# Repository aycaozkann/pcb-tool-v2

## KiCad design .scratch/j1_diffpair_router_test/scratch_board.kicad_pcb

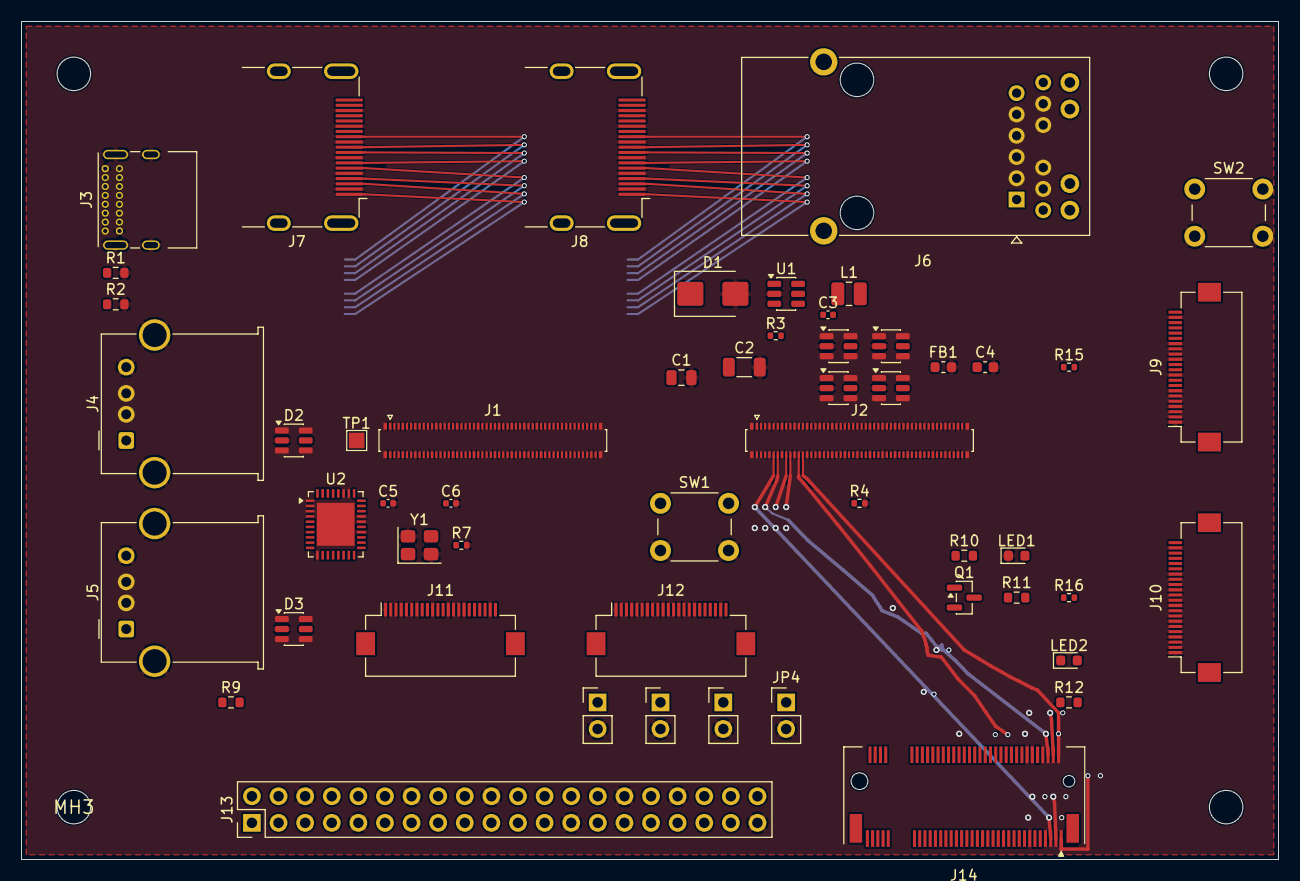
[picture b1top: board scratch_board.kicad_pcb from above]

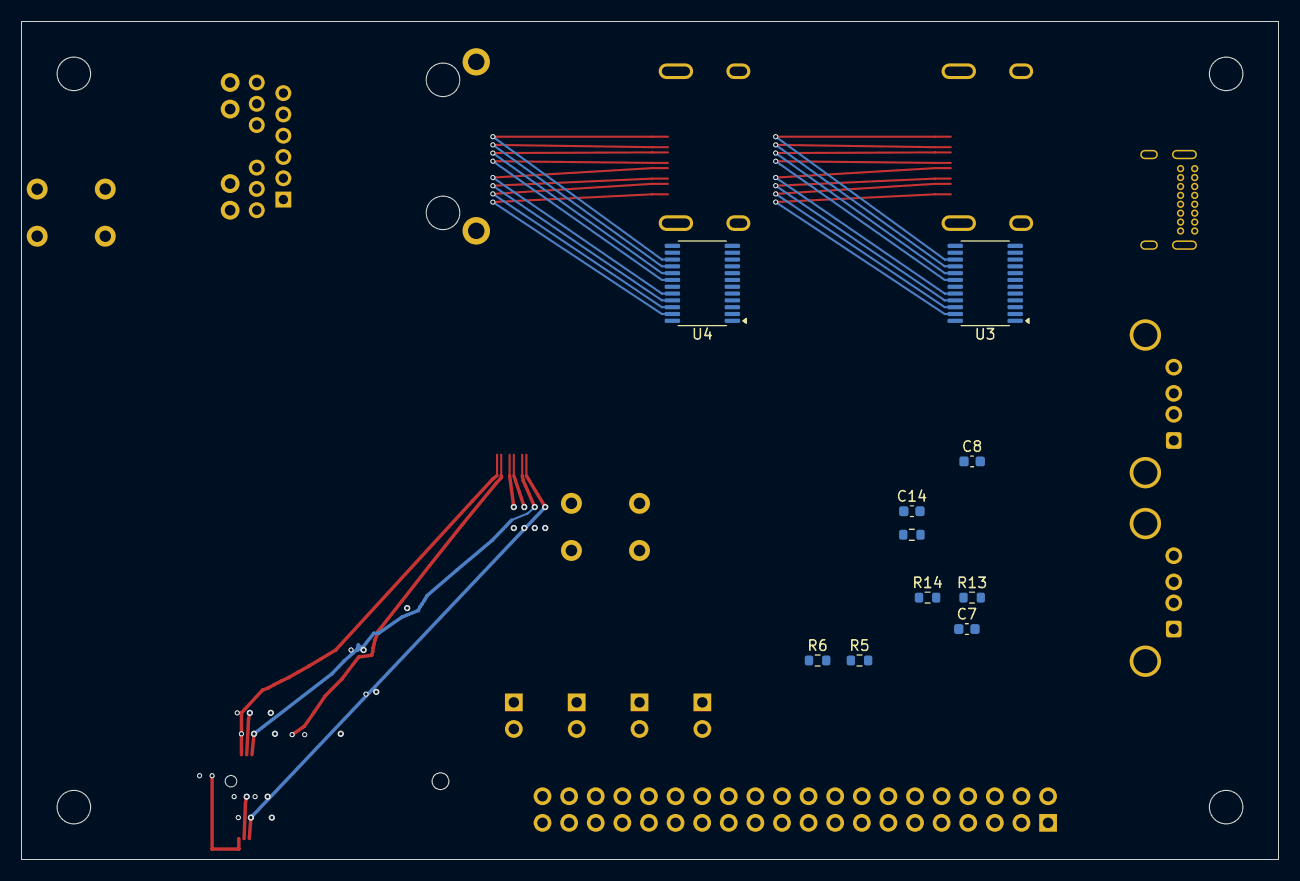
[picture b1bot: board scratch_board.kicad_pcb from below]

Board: 4 copper layers, 120.0 x 80.0 mm, 67 parts (10 on the bottom side), 155 nets.

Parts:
C1: 10uF; C_0805_2012Metric
C2: 22uF; C_1206_3216Metric
C3: 10pF; C_0402_1005Metric
C4: 100nF; C_0603_1608Metric
C5, C6: 15pF; C_0402_1005Metric
C7, C8: 1uF_TBD; C_0603_1608Metric
C14: 1uF; C_0603_1608Metric
D1: SMBJ5.0CA_5V_TVS; D_SMB
D2, D3, D4, D5, D6, D7: USBLC6-2SC6; SOT-23-6
FB1: FB_EMI; L_0603_1608Metric
J1: CM4_J1_DF40HC3.0-100DP-0.4V; Hirose_DF40C-100DP-0.4V_2x50-1MP_P0.4mm
J2: CM4_J2_DF40HC3.0-100DP-0.4V; Hirose_DF40C-100DP-0.4V_2x50-1MP_P0.4mm
J3: USB-C_PWR_IN; USB_C_Receptacle_GCT_USB4085
J4: USB-A_Port1; USB_A_Molex_67643_Horizontal
J5: USB-A_Port2; USB_A_Molex_67643_Horizontal
J6: RJ45_Gigabit_MagJack; RJ45_Pulse_JK0654219NL_Horizontal
J7: HDMI0_Connector; HDMI_A_Molex_208658-1001_Horizontal
J8: HDMI1_Connector; HDMI_A_Molex_208658-1001_Horizontal
J9: CAM0_2Lane_FPC; Hirose_FH12-22S-0.5SH_1x22-1MP_P0.50mm_Horizontal
J10: CAM1_4Lane_FPC; Hirose_FH12-22S-0.5SH_1x22-1MP_P0.50mm_Horizontal
J11: DISP0_2Lane_FPC; Hirose_FH12-22S-0.5SH_1x22-1MP_P0.50mm_Horizontal
J12: DISP1_4Lane_FPC; Hirose_FH12-22S-0.5SH_1x22-1MP_P0.50mm_Horizontal
J13: GPIO_40PIN_HEADER; PinHeader_2x20_P2.54mm_Vertical
J14: M2_KeyM_PCIe_Socket; TE_M.2_NGFF_M-KEY_1-2199230-5_H4.2_2Rows_67_P0.5mm_Horizont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
JP1: nRPIBOOT_JMP; PinHeader_1x02_P2.54mm_Vertical
JP2: WL_nDisable_JMP; PinHeader_1x02_P2.54mm_Vertical
JP3: BT_nDisable_JMP; PinHeader_1x02_P2.54mm_Vertical
JP4: EEPROM_nWP_JMP; PinHeader_1x02_P2.54mm_Vertical
L1: 2.2uH; L_1008_2520Metric
LED1: PWR_LED; LED_0603_1608Metric
LED2: ACT_LED; LED_0603_1608Metric
MH1, MH2, MH3, MH4: MountingHole_3.2mm; MountingHole_3.2mm_M3
Q1: PWR_LED_Buffer; SOT-23
R1, R2: 5.1k; R_0603_1608Metric
R3: 45.3k; R_0402_1005Metric
R4: 10k; R_0402_1005Metric
R5, R6, R11, R12: 330R; R_0603_1608Metric
R7: 12.0k_1pct; R_0402_1005Metric
R8, R10, R13, R14: 10k; R_0603_1608Metric
R9: 220R; R_0603_1608Metric
R15, R16: 2.2k; R_0402_1005Metric
SW1: RUN_Reset; SW_PUSH_6mm
SW2: GLOBAL_EN_PWR; SW_PUSH_6mm
TP1: TP_EXTRST; TestPoint_Pad_1.5x1.5mm
U1: TLV62569DBV; SOT-23-6
U2: USB2512B; QFN-36-1EP_5x6mm_P0.5mm_EP3.6x4.1mm
U3: TPD12S016_HDMI0; TSSOP-24_4.4x7.8mm_P0.65mm
U4: TPD12S016_HDMI1; TSSOP-24_4.4x7.8mm_P0.65mm
Y1: 24MHz_NX3225SA_8pF; Crystal_SMD_3225-4Pin_3.2x2.5mm

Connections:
BT_NDISABLE_JMP: J1.91, JP3.1
CAM0_C_N: J2.40, J9.14
CAM0_C_P: J2.42, J9.15
CAM0_D0_N: J2.28, J9.2
CAM0_D0_P: J2.30, J9.3
CAM0_D1_N: J2.34, J9.5
CAM0_D1_P: J2.36, J9.6
CAM0_GPIO: J1.97, J9.22
CAM1_C_N: J2.27, J10.14
CAM1_C_P: J2.29, J10.15
CAM1_D0_N: J2.15, J10.2
CAM1_D0_P: J2.17, J10.3
CAM1_D1_N: J2.21, J10.5
CAM1_D1_P: J2.23, J10.6
CAM1_D2_N: J2.33, J10.8
CAM1_D2_P: J2.35, J10.9
CAM1_D3_N: J2.39, J10.11
CAM1_D3_P: J2.41, J10.12
CARRIER_3V3: C2.1, C3.1, D4.5, D5.5, D6.5, D7.5, J9.19, J9.20, J10.19, J10.20, J11.19, J11.20, J12.19, J12.20, J14.10, J14.11, L1.2, Q1.2, R3.1, R5.1, R6.1, R8.1, R12.1, R13.1, R14.1, R15.1, R16.1, U2.5, U2.10, U2.15, U2.23, U2.27, U2.29, U2.36, U3.24, U4.24
CHASSIS_GND: FB1.1, J6.SH, J7.SH, J8.SH
CM4_3V3: J1.78, J1.84, J1.86, J13.1, J13.17
CM4_5V: C1.1, D1.1, D2.5, D3.5, J1.77, J1.79, J1.81, J1.83, J1.85, J1.87, J3.A9, J3.B9, J4.1, J5.1, J13.2, J13.4, U1.1, U1.4, U3.11, U4.11
DSI0_C_N: J2.69, J11.14
DSI0_C_P: J2.71, J11.15
DSI0_D0_N: J2.57, J11.2
DSI0_D0_P: J2.59, J11.3
DSI0_D1_N: J2.63, J11.5
DSI0_D1_P: J2.65, J11.6
DSI1_C_N: J2.87, J12.14
DSI1_C_P: J2.89, J12.15
DSI1_D0_N: J2.75, J12.2
DSI1_D0_P: J2.77, J12.3
DSI1_D1_N: J2.81, J12.5
DSI1_D1_P: J2.83, J12.6
DSI1_D2_N: J2.93, J12.8
DSI1_D2_P: J2.95, J12.9
DSI1_D3_N: J2.94, J12.11
DSI1_D3_P: J2.96, J12.12
EEPROM_WP_JMP: J1.20, JP4.1
ETH_CT: C4.1, J6.1, J6.6, J6.7, J6.12
ETH_LED1_ANODE: J6.16, R5.2
ETH_LED2_ANODE: J6.14, R6.2
ETH_LED_ACT_N: J1.15, J6.15
ETH_LED_SPD_N: J1.17, J6.13
ETH_TRD0_N: D4.1, D4.6, J1.10, J6.10
ETH_TRD0_P: D4.3, D4.4, J1.12, J6.11
ETH_TRD1_N: D5.1, D5.6, J1.6, J6.5
ETH_TRD1_P: D5.3, D5.4, J1.4, J6.4
ETH_TRD2_N: D6.1, D6.6, J1.9, J6.2
ETH_TRD2_P: D6.3, D6.4, J1.11, J6.3
ETH_TRD3_N: D7.1, D7.6, J1.5, J6.9
ETH_TRD3_P: D7.3, D7.4, J1.3, J6.8
FB_NODE: C3.2, R3.2, R4.1, U1.5
GLOBAL_EN: J1.99, SW2.1
GND: C1.2, C2.2, C4.2, C5.2, C6.2, C7.2, C8.2, C14.2, D1.2, D2.2, D3.2, D4.2, D5.2, D6.2, D7.2, FB1.2, J1.1, J1.2, J1.7, J1.8, J1.13, J1.14, J1.22, J1.23, J1.32, J1.33, J1.42, J1.43, J1.52, J1.53, J1.59, J1.60, J1.65, J1.66, J1.71, J1.74, J1.98, J2.1, J2.7, J2.8, J2.13, J2.14, J2.19, J2.20, J2.25, J2.26, J2.31, J2.32, J2.37, J2.38, J2.44, J2.50, J2.55, J2.56, J2.61, J2.62, J2.67, J2.68, J2.73, J2.74, J2.79, J2.80, J2.85, J2.86, J2.91, J2.92, J2.97, J2.98, J3.A12, J3.B12, J3.SH, J4.4, J4.SH, J5.4, J5.SH, J7.2, J7.5, J7.8, J7.11, J7.14, J7.17, J8.2, J8.5, J8.8, J8.11, J8.14, J8.17, J9.1, J9.4, J9.7, J9.10, J9.13, J9.16, J9.21, J10.1, J10.4, J10.7, J10.10, J10.13, J10.16, J10.21, J11.1, J11.4, J11.7, J11.10, J11.13, J11.16, J11.21, J12.1, J12.4, J12.7, J12.10, J12.13, J12.16, J12.21, J13.6, J13.9, J13.14, J13.20, J13.25, J13.30, J13.34, J13.39, J14.12, J14.13, J14.14, JP1.2, JP2.2, JP3.2, JP4.2, LED1.1, R1.2, R2.2, R4.2, R7.2, SW1.2, SW2.2, U1.2, U2.11, U2.22, U2.24, U2.25, U2.37, U3.5, U3.6, U3.12, U3.14, U3.19, U4.5, U4.6, U4.12, U4.14, U4.19, Y1.2, Y1.4
GPIO2: J1.58, J13.3
GPIO3: J1.56, J13.5
GPIO4: J1.54, J13.7
GPIO5: J1.34, J13.29
GPIO6: J1.30, J13.31
GPIO7: J1.37, J13.26
GPIO8: J1.39, J13.24
GPIO9: J1.40, J13.21
GPIO10: J1.44, J13.19
GPIO11: J1.38, J13.23
GPIO12: J1.31, J13.32
GPIO13: J1.28, J13.33
GPIO14: J1.55, J13.8
GPIO15: J1.51, J13.10
GPIO16: J1.29, J13.36
GPIO17: J1.50, J13.11
GPIO18: J1.49, J13.12
GPIO19: J1.26, J13.35
GPIO20: J1.27, J13.38
GPIO21: J1.25, J13.40
GPIO22: J1.46, J13.15
GPIO23: J1.47, J13.16
GPIO24: J1.45, J13.18
GPIO25: J1.41, J13.22
GPIO26: J1.24, J13.37
GPIO27: J1.48, J13.13
HDMI0_5VOUT: J7.18, U3.13
HDMI0_CEC: J2.51, U3.1
HDMI0_CEC_CONN: J7.13, U3.7
HDMI0_CLK_N: J2.90, J7.12, U3.15
HDMI0_CLK_P: J2.88, J7.10, U3.16
HDMI0_HOTPLUG: J2.53, U3.4
HDMI0_HPD_CONN: J7.19, U3.10
HDMI0_SCL: J2.100, U3.2
HDMI0_SCL_CONN: J7.15, U3.8
HDMI0_SDA: J2.99, U3.3
HDMI0_SDA_CONN: J7.16, U3.9
HDMI0_TX0_N: J2.84, J7.9, U3.17
HDMI0_TX0_P: J2.82, J7.7, U3.18
HDMI0_TX1_N: J2.78, J7.6, U3.20
HDMI0_TX1_P: J2.76, J7.4, U3.21
HDMI0_TX2_N: J2.72, J7.3, U3.22
HDMI0_TX2_P: J2.70, J7.1, U3.23
HDMI1_5VOUT: J8.18, U4.13
HDMI1_CEC: J2.49, U4.1
HDMI1_CEC_CONN: J8.13, U4.7
HDMI1_CLK_N: J2.66, J8.12, U4.15
HDMI1_CLK_P: J2.64, J8.10, U4.16
HDMI1_HOTPLUG: J2.43, U4.4
HDMI1_HPD_CONN: J8.19, U4.10
HDMI1_SCL: J2.47, U4.2
HDMI1_SCL_CONN: J8.15, U4.8
HDMI1_SDA: J2.45, U4.3
HDMI1_SDA_CONN: J8.16, U4.9
HDMI1_TX0_N: J2.60, J8.9, U4.17
HDMI1_TX0_P: J2.58, J8.7, U4.18
HDMI1_TX1_N: J2.54, J8.6, U4.20
HDMI1_TX1_P: J2.52, J8.4, U4.21
HDMI1_TX2_N: J2.48, J8.3, U4.22
HDMI1_TX2_P: J2.46, J8.1, U4.23
I2C_CAMDISP_SCL: J1.80, J10.17, J12.17, R15.2
I2C_CAMDISP_SDA: J1.82, J10.18, J12.18, R16.2
ID_SC: J1.35, J9.17, J11.17, J13.28
ID_SD: J1.36, J9.18, J11.18, J13.27
LED1_ANODE_NODE: LED1.2, R11.2
LED2_ANODE_NODE: LED2.2, R12.2
LED_ACT_N: J1.21, LED2.1
NEXTRST: J1.100, TP1.1
NRPIBOOT_JMP: J1.93, JP1.1
PCIE_CLKREQ_N: J2.2, J14.8
PCIE_PERST_N: J2.9, J14.7
PCIE_REFCLK_N: J2.12, J14.6
PCIE_REFCLK_P: J2.10, J14.5
PCIE_RX_N: J2.18, J14.4
PCIE_RX_P: J2.16, J14.3
PCIE_TX_N: J2.24, J14.2
PCIE_TX_P: J2.22, J14.1
PI_LED_NPWR: J1.95, R10.1
Q1_BASE_NODE: Q1.1, R10.2
R11_Q1_NODE: Q1.3, R11.1
RUN_PG: J1.92, R9.1
SW1_R9_NODE: R9.2, SW1.1
SW_NODE: L1.1, U1.3
USBC_CC1: J1.96, J3.A5, R1.1
USBC_CC2: J1.94, J3.B5, R2.1
USBHUB_CRFILT: C7.1, U2.14
USBHUB_OCS_N1: R13.2, U2.13
USBHUB_OCS_N2: R14.2, U2.17
USBHUB_PLLFILT: C8.1, U2.34
USBHUB_RBIAS: R7.1, U2.35
USBHUB_RESET_N: C14.1, R8.2, U2.26
USBHUB_XTAL_IN: C5.1, U2.33, Y1.1
USBHUB_XTAL_OUT: C6.1, U2.32, Y1.3
USB_A1_DM: D2.1, D2.6, J4.2, U2.1
USB_A1_DP: D2.3, D2.4, J4.3, U2.2
USB_A2_DM: D3.1, D3.6, J5.2, U2.3
USB_A2_DP: D3.3, D3.4, J5.3, U2.4
USB_N: J2.3, U2.30
USB_P: J2.5, U2.31
WL_NDISABLE_JMP: J1.89, JP2.1
